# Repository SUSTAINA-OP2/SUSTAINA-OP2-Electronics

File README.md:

<h1 align="center">
    Printed Circuit Boards for SUSTAINA-OP2&trade;
</h1>
<table align="center">
    <tr>
        <td align="center"><a href="./SUSTAINA-Constant-Voltage-Board">Constant Voltage Board</a></td>
        <td align="center"><a href="./SUTAINA-Control-Switches-Board">Control Switches Board</a></td>
        <td align="center"><a href="./SUSTAINA-PMX-Control-Board">PMX Control Board</a></td>
    </tr>
    <tr>
        <td align="center"></td>
        <td align="center"></td>
        <td align="center"></td>
    </tr>
    <tr>
        <td align="center"><a href="./SUSTAINA-Power-Logging-Board">Power Logging Board</a></td>
        <td align="center"><a href="./SUSTAINA-Power-Distribution-Board">Power Distribution Board</a></td>
        <td align="center"><a href="./SUSTAINA-Power-Supply-Switching-Board">Power Supply Switching Board</a></td>
    </tr>
    <tr>
        <td align="center"></td>
        <td align="center"></td>
        <td align="center"></td>
    </tr>
    <tr>
        <td align="center"><a href="./SUSTAINA-SBC-Power-Board">SBC Power Board</a></td>
        <td align="center"><a href="./SUSTAINA-SCI-Extension-Board">SCI Extension Board</a></td>
        <td align="center"><a href="./SUSTAINA-StrainGauge-Sensing-Board">Strain Gauge Sensing Board</a></td>
    </tr>
    <tr>
        <td align="center"></td>
        <td align="center"></td>
        <td align="center"></td>
    </tr>
    <tr>
        <td align="center"><a href="./SUSTAINA-Power-Monitor-Module">Power Monitor Module</a></td>
        <td align="center"><a href="./SUSTAINA-USB-to-Quad-RS-485-Conv-Module">USB to Quad RS-485 Conv. Module</a></td>
        <td align="center"></td>
    </tr>
    <tr>
        <td align="center"></td>
        <td align="center"></td>
        <td align="center"></td>
    </tr>
</table>

> [!NOTE]
> This repository provides design and order data for PCBs of SUSTAINA-OP2&trade;.<br>
> Other SUSTAINA-OP2&trade; contents
> - Mechanical: https://github.com/SUSTAINA-OP/SUSTAINA-OP2
> - Firmware: https://github.com/SUSTAINA-OP/SUSTAINA-OP2-Firmware

## Features of SUSTAINA-OP2&trade;'s PCBs

All PCBs for SUSTAINA-OP are compatible with PCBA, which can reduce production barriers (such as selecting and assembling electronic components) before they are assembled into robots.

The PCB fabrication and PCBA used for all SUSTAINA-OP2 are outsourced to JLCPCB!

> [!WARNING]
> Some components to be assembled on the PCB (e.g. not in stock or not handled)  cannot be assembled using PCBA and must be assembled by yourself.

## Repository Contents

The PCBs of SUSTAINA-OP2&trade; can be divided into two main categories.<br>
The first is "module," which packages sensors, conversion circuits, etc. in functional units on a single board and can be easily replaced.<br>
The second is "board", which is a multifunctional PCB with modules and other components.

### Boards
- [Constant Voltage Board](./SUSTAINA-Constant-Voltage-Board)
- [Control Switches Board](./SUTAINA-Control-Switches-Board)
- [PMX Control Board](./SUSTAINA-PMX-Control-Board)
- [Power Logging Board](./SUSTAINA-Power-Logging-Board)
- [Power Distribution Board](./SUSTAINA-Power-Distribution-Board)
- [Power Supply Switching Board](./SUSTAINA-Power-Supply-Switching-Board)
- [SBC Power Board](./SUSTAINA-SBC-Power-Board)
- [SCI Extension Board](./SUSTAINA-SCI-Extension-Board)
- [StrainGauge Sensing Board](./SUSTAINA-StrainGauge-Sensing-Board)

### Modules
- [Power Monitor Module](./SUSTAINA-Power-Monitor-Module)
- [USB to Quad RS-485 Conv. Module](./SUSTAINA-USB-to-Quad-RS-485-Conv-Module)

## Development Environment
The PCBs for SUSTAINA-OP2&trade; were designed in **Autodesk Eagle 9.6.2**.

## License Information
This product is open source. Please review the [LICENSE(EN)](/LICENSE) / [LICENSE(JA)](/LICENSE-JA) for license information.

This product by Masato Kubotera is licensed under a [CC BY-NC-SA 4.0 DEED](http://creativecommons.org/licenses/by-nc-sa/4.0/).

> [!NOTE]
> **Summary:**
> - **Attribution** — You must give appropriate credit , provide a link to the license, and indicate if changes were made.
> - **NonCommercial** — You may not use the material for commercial purposes.
> - **ShareAlike** — If you remix, transform, or build upon the material, you must distribute your contributions under the same license as the original.

> [!TIP]
> - **Examples of appropriate credit** — [SUSTAINA-OP2&trade;](https://github.com/SUSTAINA-OP/SUSTAINA-OP) &copy; Masato Kubotera (2024) CC BY-NC-SA 4.0 DEED
> >
> - **Reference & Citation**  
>   To reference and/or cite the work contained in this repository, please use the following publications:
>   - Kubotera, M. and Hayashibara, Y.: SUSTAINA-OP&trade;: Kid-sized Open Hardware Platform Humanoid Robot with Emphasis on Sustainability. RoboCup 2023: Robot World Cup XXVI, pp.166–178 (2024) [Springer](https://link.springer.com/chapter/10.1007/978-3-031-55015-7_14)
>
>     **The paper is about SUSTAINA-OP&trade;. Publications on SUSTAINA-OP2&trade; will be published soon.**

## Contact
If you have any questions, please contact the designer of this product, Masato Kubodera, by [E-mail](masatokubotera06@yahoo.co.jp).

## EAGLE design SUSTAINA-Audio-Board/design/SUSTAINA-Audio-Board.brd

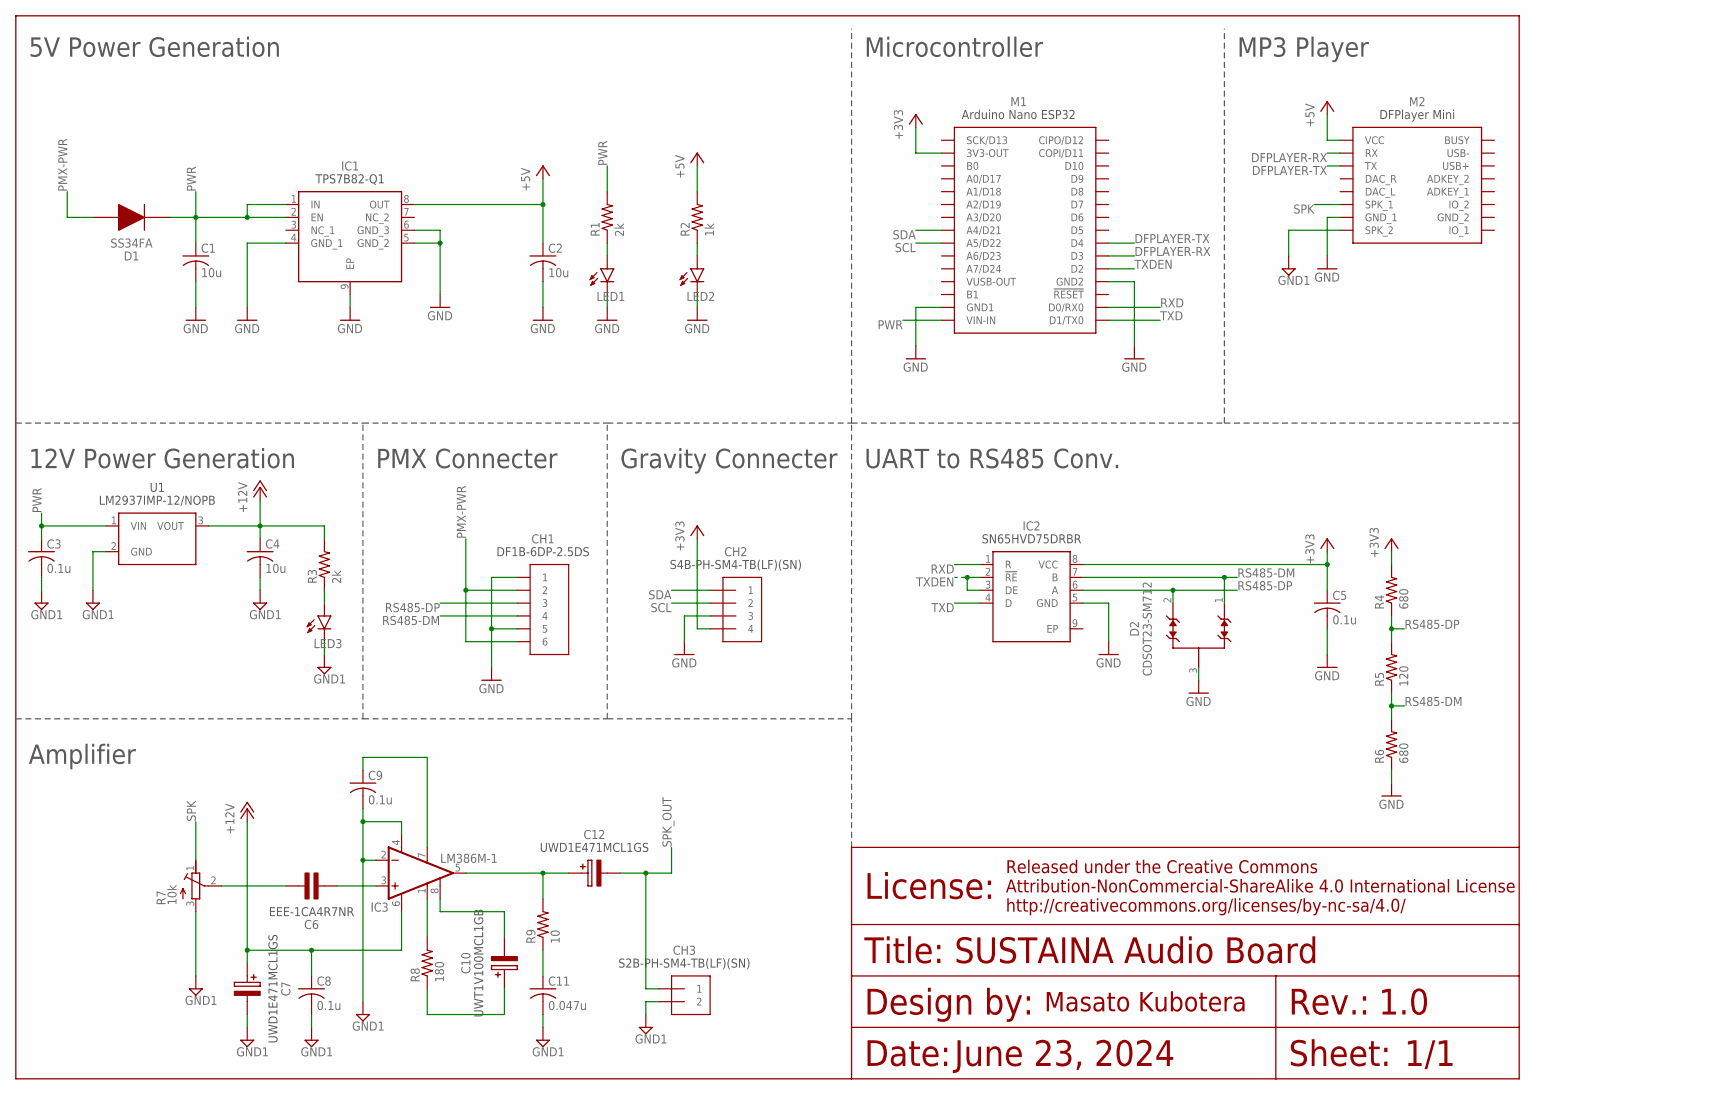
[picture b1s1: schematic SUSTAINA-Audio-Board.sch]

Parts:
C1, C2, C4: 10u; C0603
C3, C5, C8, C9: 0.1u; C0603
C6: EEE-1CA4R7NR
C7, C12: UWD1E471MCL1GS
C10: UWT1V100MCL1GB
C11: 0.047u; C050-055X075
CH1: DF1B-6DP-2.5DS
CH2: S4B-PH-SM4-TB(LF)(SN)
CH3: S2B-PH-SM4-TB(LF)(SN)
D1: SS34FA
D2: CDSOT23-SM712; SOT-23-3
IC1: TPS7B82-Q1; SOP65P490X110-9N
IC2: SN65HVD75DRBR; SON65P300X300X100-9N
IC3: LM386M-1; SO08
LED1, LED2, LED3: LEDSML0603; SML0603
M1: NANO-ESP32
M2: DFPLAYER_MINI
R1, R3: 2k; R0603
R2: 1k; R0603
R4, R6: 680; R0603
R5: 120; R0603
R7: 10k; RTRIM3006P
R8: 180; R0603
R9: 10; R0603
U1: LM2937IMP-12NOPB; SOT-223

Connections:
+3V3: C5.1, CH2.4, IC2.8 (VCC), M1.3V3-OUT, R4.2
+5V: C2.1, IC1.8 (OUT), M2.VCC, R2.2
+12V: C4.1, C7.+, C8.1, IC3.6 (VS), R3.2, U1.3 (VOUT)
DFPLAYER-RX: M1.D3, M2.RX
DFPLAYER-TX: M1.D4, M2.TX
GND: C1.2, C2.2, C5.2, CH1.1, CH1.5, CH2.3, D2.3, IC1.4 (GND_1), IC1.5 (GND_2), IC1.6 (GND_3), IC1.9 (EP), IC2.5 (GND), LED1.C, LED2.C, M1.GND1, M1.GND2, M2.GND_1, R6.1
GND1: C3.2, C4.2, C7.-, C8.2, C9.2, C11.2, CH3.2, IC3.2 (-IN), IC3.4 (GND), LED3.C, M2.SPK2 (SPK_2), R7.3 (A), U1.2 (GND)
LED-5V: LED2.A, R2.1
LED-12V: LED3.A, R3.1
LED-VIN: LED1.A, R1.1
LM386_1: IC3.1 (GAIN), R8.2
LM386_1-8: C10.+, R8.1
LM386_3: C6.1, IC3.3 (+IN)
LM386_3_: C6.2, R7.2 (S)
LM386_7: C9.1, IC3.7 (BYPASS)
LM386_8: C10.-, IC3.8 (GAIN)
PMX-PWR: CH1.2, CH1.6, D1.2
PWR: C1.1, C3.1, D1.1, IC1.1 (IN), IC1.2 (EN), M1.VIN-IN, R1.2, U1.1 (VIN)
RS485-DM: CH1.4, D2.1, IC2.7 (B), R5.1, R6.2
RS485-DP: CH1.3, D2.2, IC2.6 (A), R4.1, R5.2
RXD: IC2.1 (R), M1.D0/RX0
SCL: CH2.2, M1.A5/D22
SDA: CH2.1, M1.A4/D21
SPK: M2.SPK1 (SPK_1), R7.1 (E)
SPK_OUT: C12.-, CH3.1
SPK_OUT_: C12.+, IC3.5 (OUT), R9.2
SPK_OUT__: C11.1, R9.1
TXD: IC2.4 (D), M1.D1/TX0
TXDEN: IC2.2 (!RE), IC2.3 (DE), M1.D2

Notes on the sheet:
1.0
1/1
June 23, 2024
SUSTAINA Audio Board
5V Power Generation
12V Power Generation
PMX Connecter
Gravity Connecter
Amplifier
UART to RS485 Conv.
Microcontroller
MP3 Player

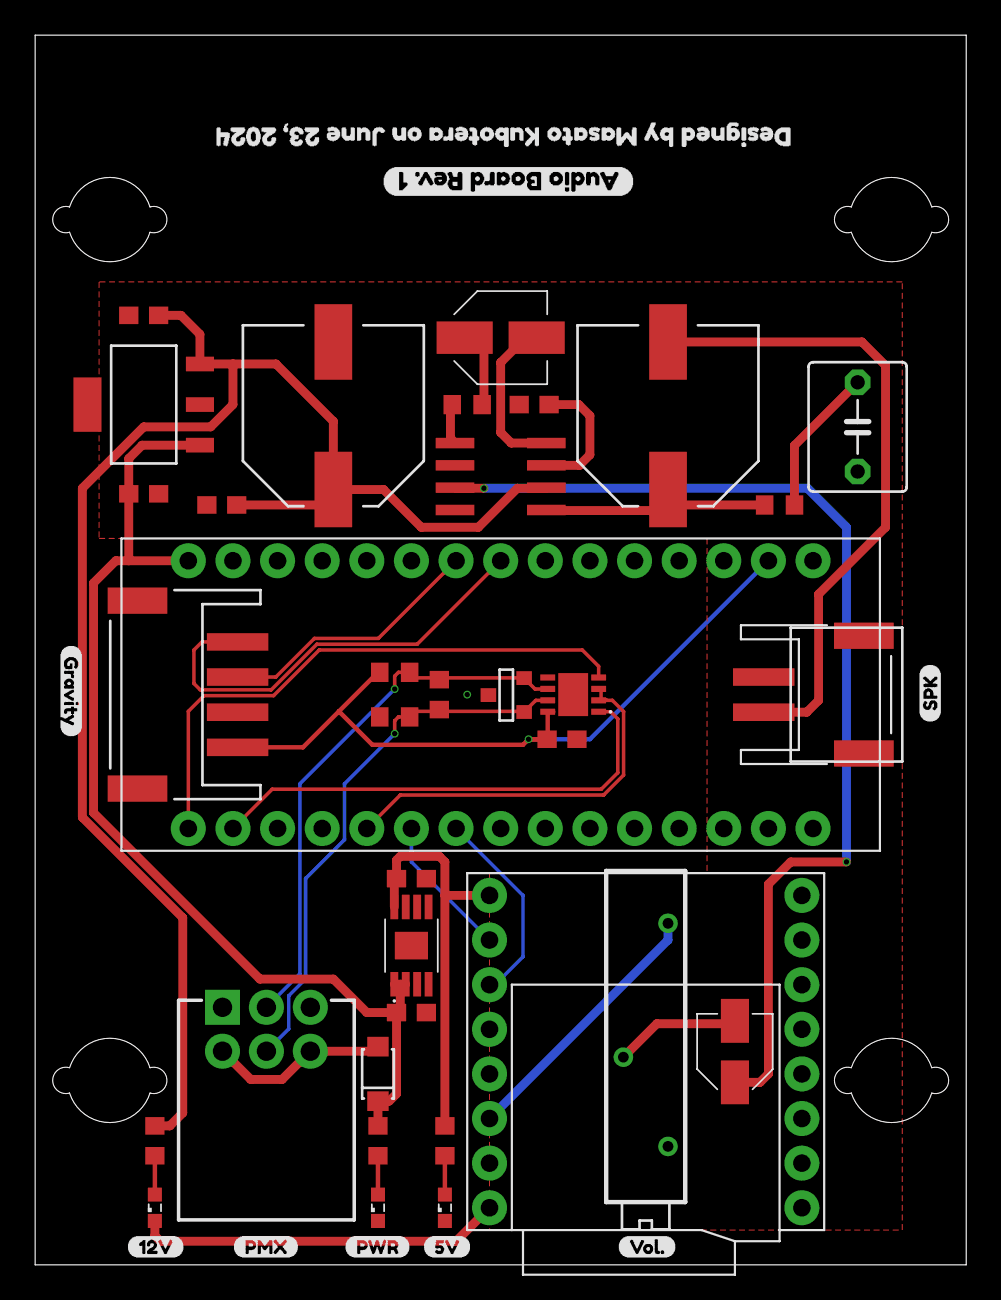
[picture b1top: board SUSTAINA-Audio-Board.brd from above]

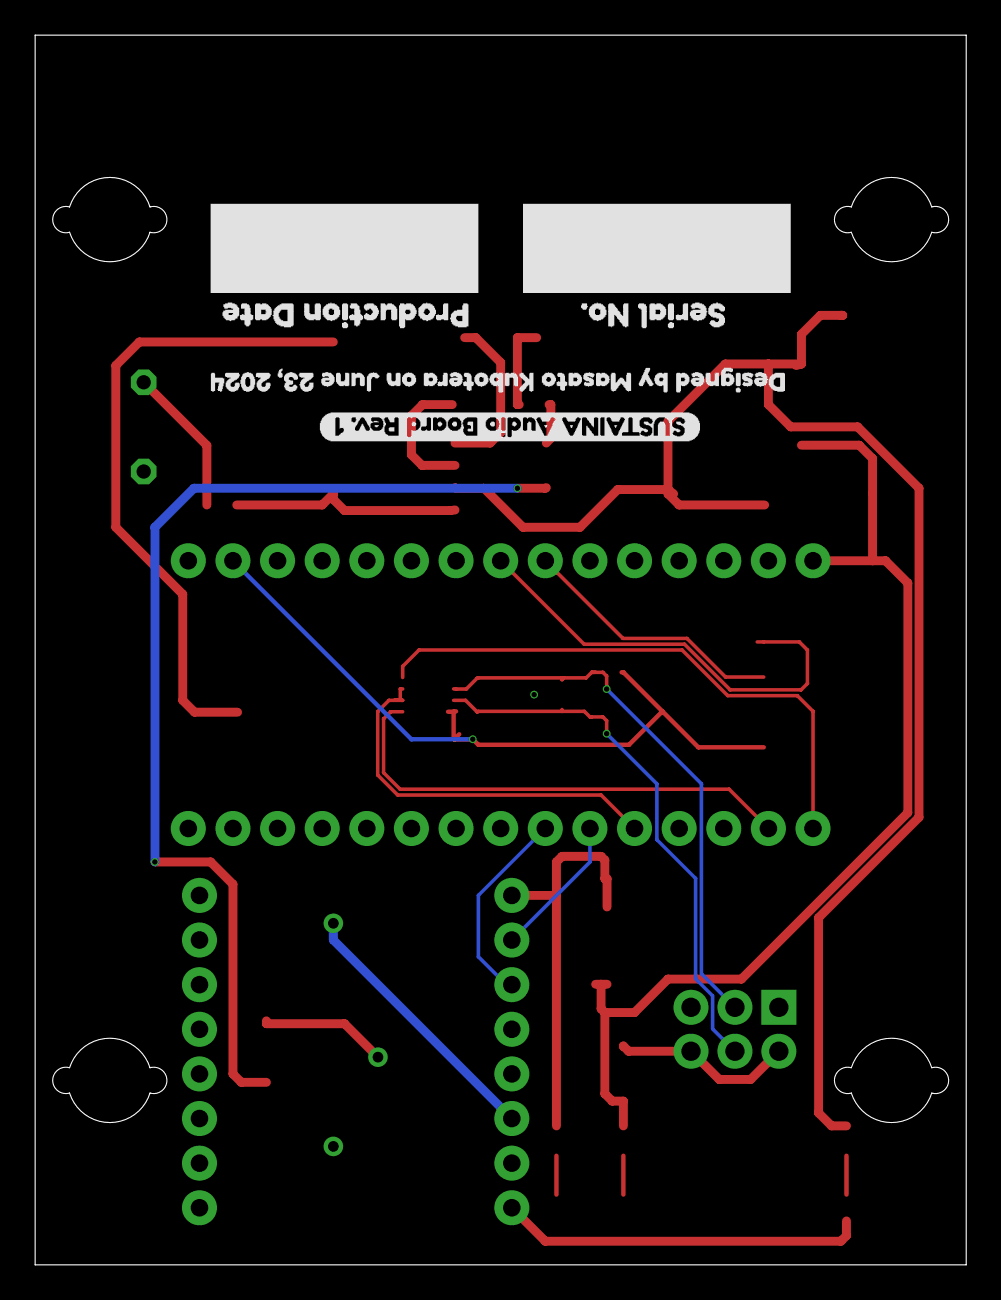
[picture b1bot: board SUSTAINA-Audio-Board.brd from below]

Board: 2 copper layers, 53.0 x 70.0 mm, 48 parts (4 on the bottom side), 29 nets.

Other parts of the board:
U$1: GRAVITY-0.03
U$2, U$11: DESIGNED_BY_MASATO_KUBOTERA_ON_JUNE_23
U$3: 12V-0.03
U$4: 5V-0.03
U$5: PMX-0.03
U$6: PWR-0.03
U$7: VOL#-0.03
U$8: SPK-0.03
U$9: SUSTAINA_AUDIO_BOARD_REV#_1
U$10: AUDIO_BOARD_REV#_1
U$12: PRODUCTION_DATE0
U$13: SERIAL_NO#0

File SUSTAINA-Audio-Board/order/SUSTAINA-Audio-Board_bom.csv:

Comment,Designator,Footprint,LCSC Part #
10u,C1 C2 C4,C0603,C86275
UWT1V100MCL1GB,C10,UWT1V100MCL1GB,C445058
0.1u,C3 C5 C8 C9,C0603,C80516
EEE-1CA4R7NR,C6,EEE-1CA4R7NR,C401604
UWD1E471MCL1GS,C7 C12,UWD1E471MCL1GS,C251022
S4B-PH-SM4-TB(LF)(SN),CH2,S4B-PH-SM4-TB(LF)(SN),C265102
S2B-PH-SM4-TB(LF)(SN),CH3,S2B-PH-SM4-TB(LF)(SN),C295747
SS34FA,D1,SS34FA,C719833
CDSOT23-SM712,D2 ,CDSOT23-SM712,C404012
TPS7B82-Q1,IC1,SOP65P490X110-9N,C424924
SN65HVD75DRBR,IC2,SON65P300X300X100-9N,C98708
LM386M-1,IC3,SO08,C5375298
Green,LED1 LED2 LED3,SML0603,C2922668
2k,R1 R3,R0603,C2097078
1k,R2,R0603,C22548
680,R4 R6,R0603,C112310
120,R5,R0603,C114640
180,R8,R0603,C137786
10,R9,R0603,C109318
LM2937IMP-12NOPB,U1,SOT-223,C5220609

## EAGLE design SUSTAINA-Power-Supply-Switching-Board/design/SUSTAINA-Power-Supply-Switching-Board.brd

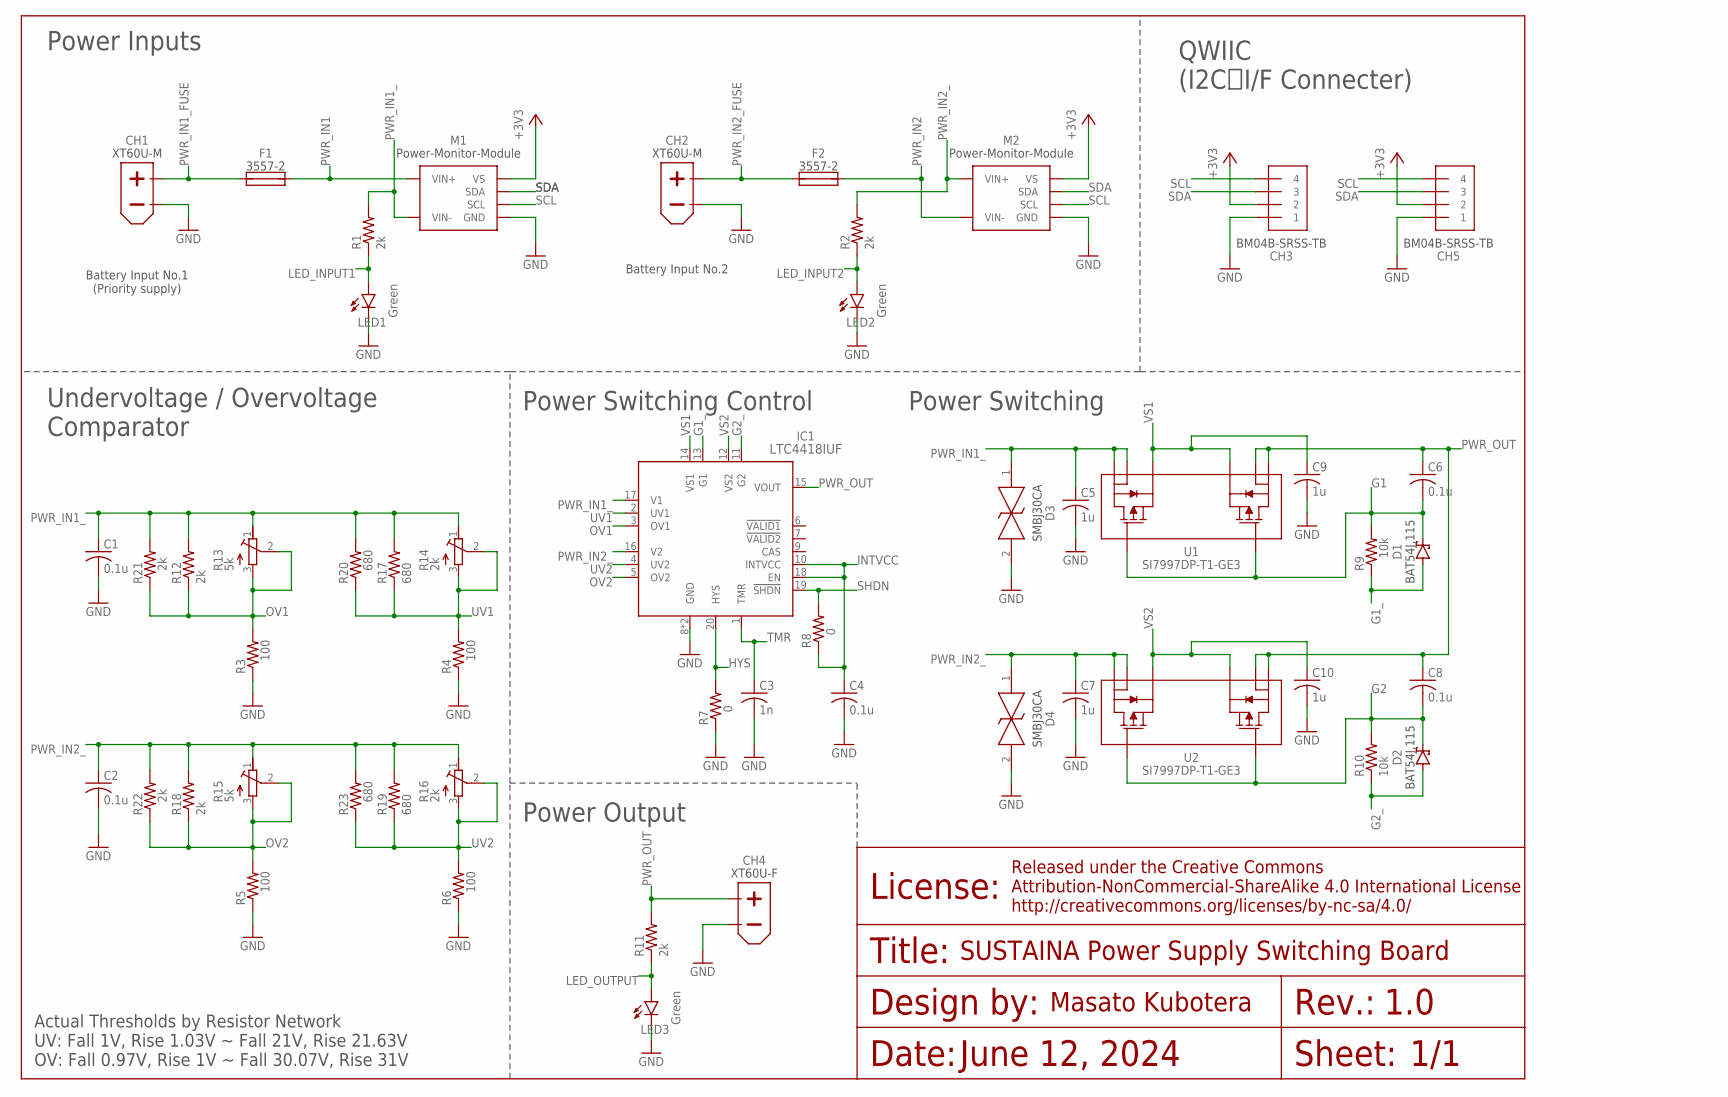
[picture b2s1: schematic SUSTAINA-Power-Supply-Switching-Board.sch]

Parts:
C1, C2, C4, C6, C8: 0.1u; C0603
C3: 1n; C0603
C5, C7, C9, C10: 1u; C0603
CH1, CH2: XT60U-M
CH3, CH5: BM04B-SRSS-TB
CH4: XT60U-F
D1, D2: BAT54J,115; SOD-323-2
D3, D4: SMBJ30CA
F1, F2: 3557-2
IC1: LTC4418IUF
LED1, LED2, LED3: Green; SML0603
M1, M2: POWER-MONITOR-MODULE
R1, R2, R11, R21, R22: 2k; R0603
R3, R4, R5, R6: 100; R0603
R7, R8: 0; R0603
R9, R10: 10k; R0603
R12, R18: 2k; 0204/5
R13, R15: 5k; RTRIM3006P
R14, R16: 2k; RTRIM3006P
R17, R19: 680; 0204/5
R20, R23: 680; R0603
U1, U2: SI7997DP-T1-GE3; POWERPAK_SO-8_VIS

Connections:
+3V3: CH3.2, CH5.2, M1.VS, M2.VS
G1: C6.2, D1.1 (C), R9.2, U1.2 (G1), U1.4 (G2)
G1_: D1.2 (A), IC1.13 (G1), R9.1
G2: C8.2, D2.1 (C), R10.2, U2.2 (G1), U2.4 (G2)
G2_: D2.2 (A), IC1.11 (G2), R10.1
GND: C1.2, C2.2, C3.2, C4.2, C5.2, C7.2, C9.2, C10.2, CH1.-, CH2.-, CH3.1, CH4.-, CH5.1, D3.2, D4.2, IC1.8 (GND), IC1.21 (GND), LED1.C, LED2.C, LED3.C, M1.GND, M2.GND, R3.1, R4.1, R5.1, R6.1, R7.1
HYS: IC1.20 (HYS), R7.2
INTVCC: C4.1, IC1.10 (INTVCC), IC1.18 (EN), R8.1
LED_INPUT1: LED1.A, R1.1
LED_INPUT2: LED2.A, R2.1
LED_OUTPUT: LED3.A, R11.1
OV1: IC1.3 (OV1), R3.2, R12.1, R13.2 (S), R13.3 (A), R21.1
OV2: IC1.5 (OV2), R5.2, R15.2 (S), R15.3 (A), R18.1, R22.1
PWR_IN1: F1.3 (2), F1.4 (2), M1.VIN+1 (VIN+), M1.VIN+2 (VIN+), M1.VIN+3 (VIN+), M1.VIN+4 (VIN+), M1.VIN+5 (VIN+), M1.VIN+6 (VIN+), M1.VIN+7 (VIN+), M1.VIN+8 (VIN+), M1.VIN+9 (VIN+), M1.VIN+10 (VIN+)
PWR_IN1_: C1.1, C5.1, D3.1, IC1.17 (V1), M1.VIN-1 (VIN-), M1.VIN-2 (VIN-), M1.VIN-3 (VIN-), M1.VIN-4 (VIN-), M1.VIN-5 (VIN-), M1.VIN-6 (VIN-), M1.VIN-7 (VIN-), M1.VIN-8 (VIN-), M1.VIN-9 (VIN-), M1.VIN-10 (VIN-), R1.2, R12.2, R13.1 (E), R14.1 (E), R17.2, R20.2, R21.2, U1.5 (D2), U1.6 (D2_2)
PWR_IN1_FUSE: CH1.+, F1.1, F1.2 (1)
PWR_IN2: F2.3 (2), F2.4 (2), M2.VIN-1 (VIN-), M2.VIN-2 (VIN-), M2.VIN-3 (VIN-), M2.VIN-4 (VIN-), M2.VIN-5 (VIN-), M2.VIN-6 (VIN-), M2.VIN-7 (VIN-), M2.VIN-8 (VIN-), M2.VIN-9 (VIN-), M2.VIN-10 (VIN-)
PWR_IN2_: C2.1, C7.1, D4.1, IC1.16 (V2), M2.VIN+1 (VIN+), M2.VIN+2 (VIN+), M2.VIN+3 (VIN+), M2.VIN+4 (VIN+), M2.VIN+5 (VIN+), M2.VIN+6 (VIN+), M2.VIN+7 (VIN+), M2.VIN+8 (VIN+), M2.VIN+9 (VIN+), M2.VIN+10 (VIN+), R2.2, R15.1 (E), R16.1 (E), R18.2, R19.2, R22.2, R23.2, U2.7 (D1), U2.8 (D1_2)
PWR_IN2_FUSE: CH2.+, F2.1, F2.2 (1)
PWR_OUT: C6.1, C8.1, CH4.+, IC1.15 (VOUT), R11.2, U1.7 (D1), U1.8 (D1_2), U2.5 (D2), U2.6 (D2_2)
SCL: CH3.4, CH5.4, M1.SCL, M2.SCL
SDA: CH3.3, CH5.3, M1.SDA, M2.SDA
SHDN: IC1.19 (!SHDN), R8.2
TMR: C3.1, IC1.1 (TMR)
UV1: IC1.2 (UV1), R4.2, R14.2 (S), R14.3 (A), R17.1, R20.1
UV2: IC1.4 (UV2), R6.2, R16.2 (S), R16.3 (A), R19.1, R23.1
VS1: C9.1, IC1.14 (VS1), U1.1 (S1), U1.3 (S2)
VS2: C10.1, IC1.12 (VS2), U2.1 (S1), U2.3 (S2)

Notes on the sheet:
Battery Input No.1 (Priority supply)
Battery Input No.2
Actual Thresholds by Resistor Network UV: Fall 1V, Rise 1.03V ~ Fall 21V, Rise 21.63V OV: Fall 0.97V, Rise 1V ~ Fall 30.07V, Rise 31V
1.0
1/1
June 12, 2024
SUSTAINA Power Supply Switching Board
Power Inputs
Undervoltage / Overvoltage Comparator
Power Switching Control
Power Switching
QWIIC (I2C I/F Connecter)
Power Output

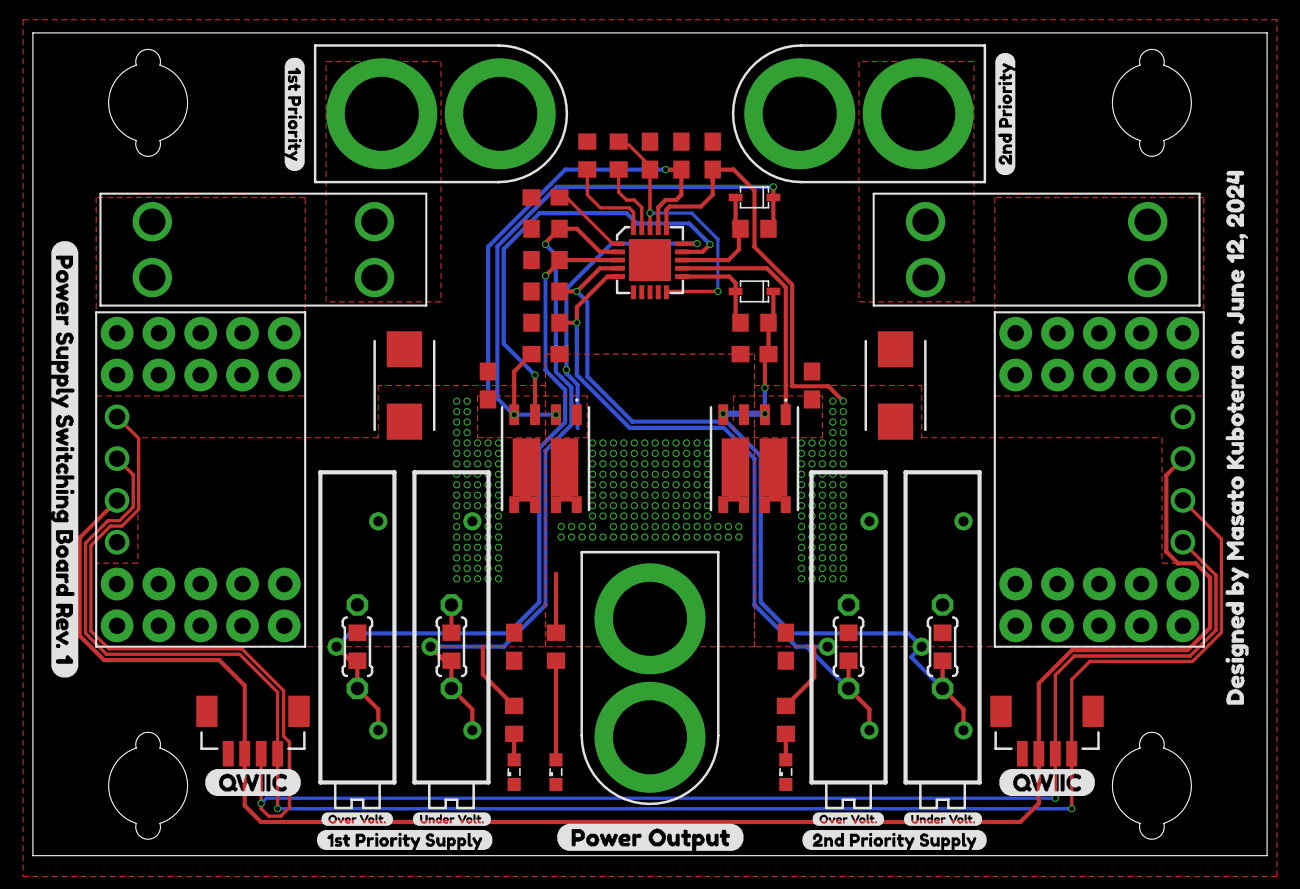
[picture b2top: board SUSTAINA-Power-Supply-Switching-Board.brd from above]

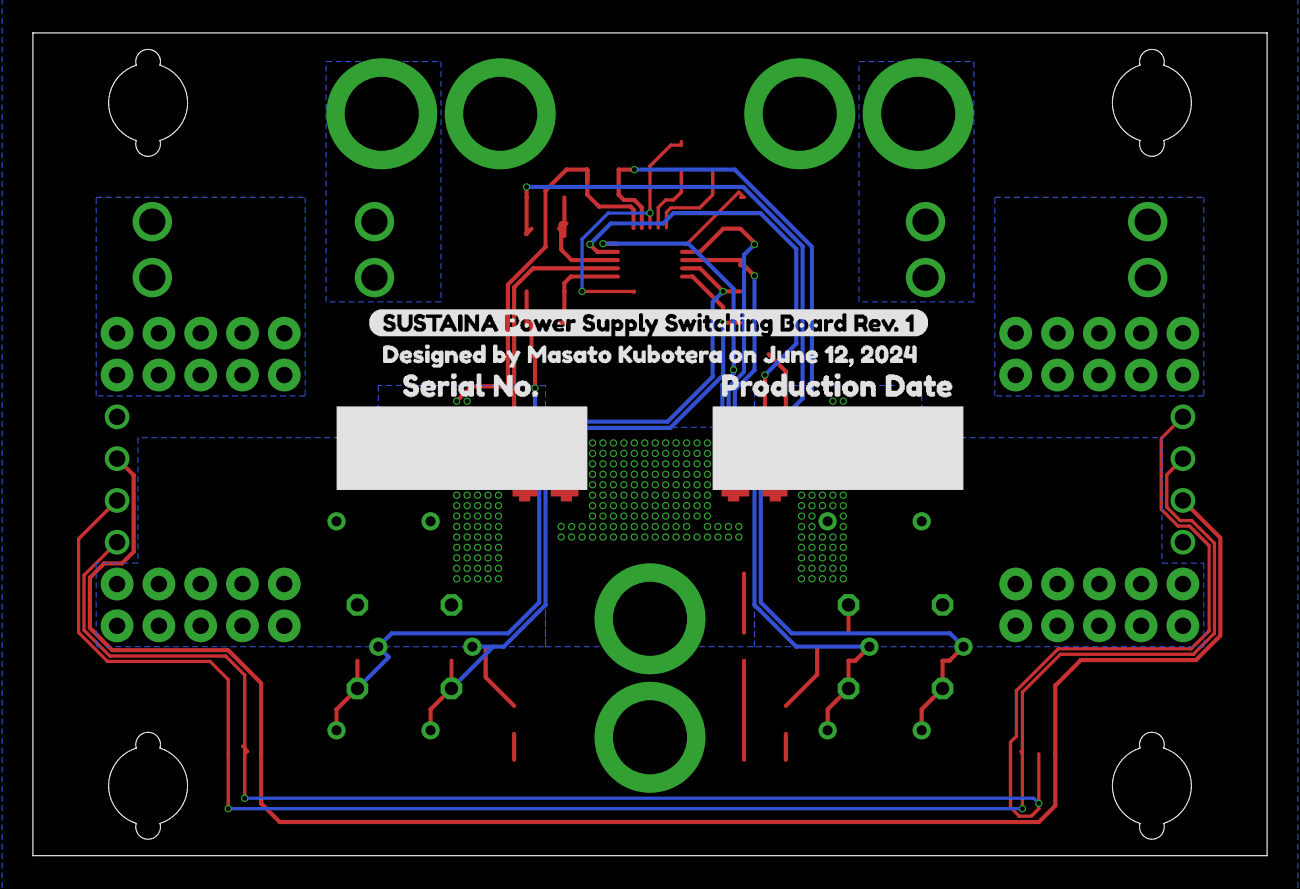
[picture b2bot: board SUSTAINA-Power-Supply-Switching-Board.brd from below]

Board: 2 copper layers, 75.0 x 50.0 mm, 69 parts (4 on the bottom side), 28 nets.

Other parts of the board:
U$1: SUSTAINA_POWER_SUPPLY_SWITCHING_BOARD_REV#_1
U$2, U$15: DESIGNED_BY_MASATO_KUBOTERA_ON_JUNE_12
U$3: 1ST_PRIORITY
U$4: 2ND_PRIORITY
U$5: POWER_OUTPUT0
U$6: 1ST_PRIORITY_SUPPLY1
U$7: 2ND_PRIORITY_SUPPLY1
U$8, U$9: UNDER_VOLT#0
U$10, U$11: OVER_VOLT#0
U$12, U$13: QWIIC0
U$14: POWER_SUPPLY_SWITCHING_BOARD_REV#_1
U$16: SERIAL_NO#0
U$29: PRODUCTION_DATE0

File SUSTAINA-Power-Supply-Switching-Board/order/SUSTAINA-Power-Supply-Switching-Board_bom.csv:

Comment,Designator,Footprint,LCSC Part #
0,R7 R8,R0603,C100044
0.1u,C1 C2 C4 C6 C8,C0603,C2929177
1n,C3,C0603,C153291
1u,C5 C7 C9 C10,C0603,C86020
2k,R1 R2 R11 R21 R22,R0603,C2097078
10k,R9 R10,R0603,C98220
100,R3 R4 R5 R6,R0603,C105588
680,R20 R23,R0603,C112310
BAT54J 115,D1,SOD-323-2,C130415
BAT54J 115,D2,SOD-323-2,C130415
BM04B-SRSS-TB,CH3 CH5,BM04B-SRSS-TB,C160390
Green,LED1 LED2 LED3,SML0603,C2922668
LTC4418IUF,IC1,LTC4418IUF,C580908
SI7997DP-T1-GE3,U1 U2,POWERPAK_SO-8_VIS,C913432
SMBJ30CA,D3 D4,SMBJ30CA,C83847

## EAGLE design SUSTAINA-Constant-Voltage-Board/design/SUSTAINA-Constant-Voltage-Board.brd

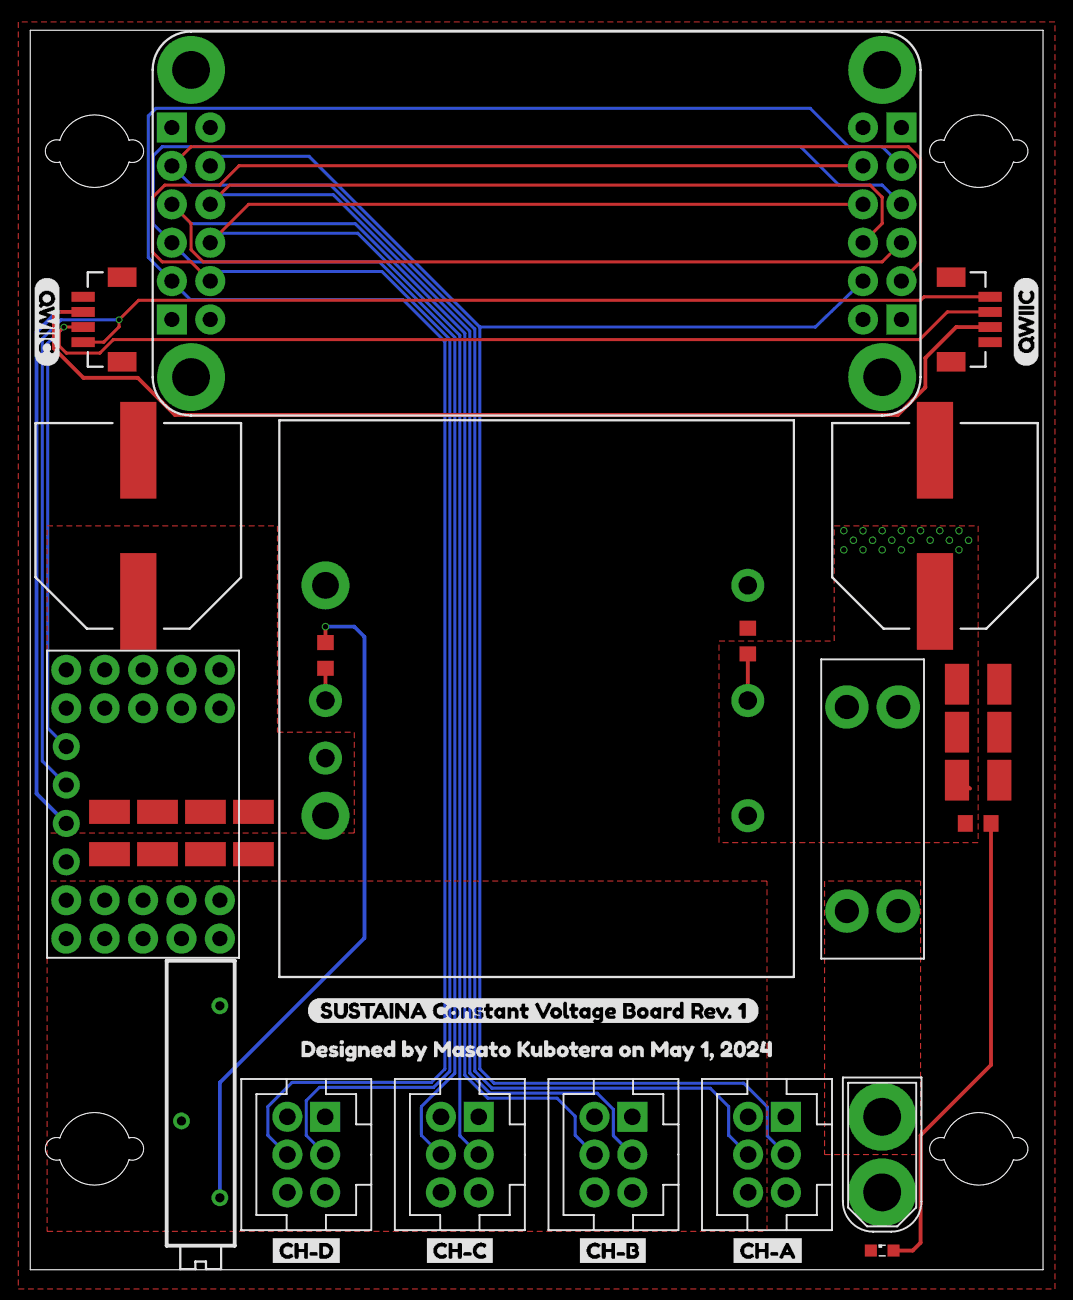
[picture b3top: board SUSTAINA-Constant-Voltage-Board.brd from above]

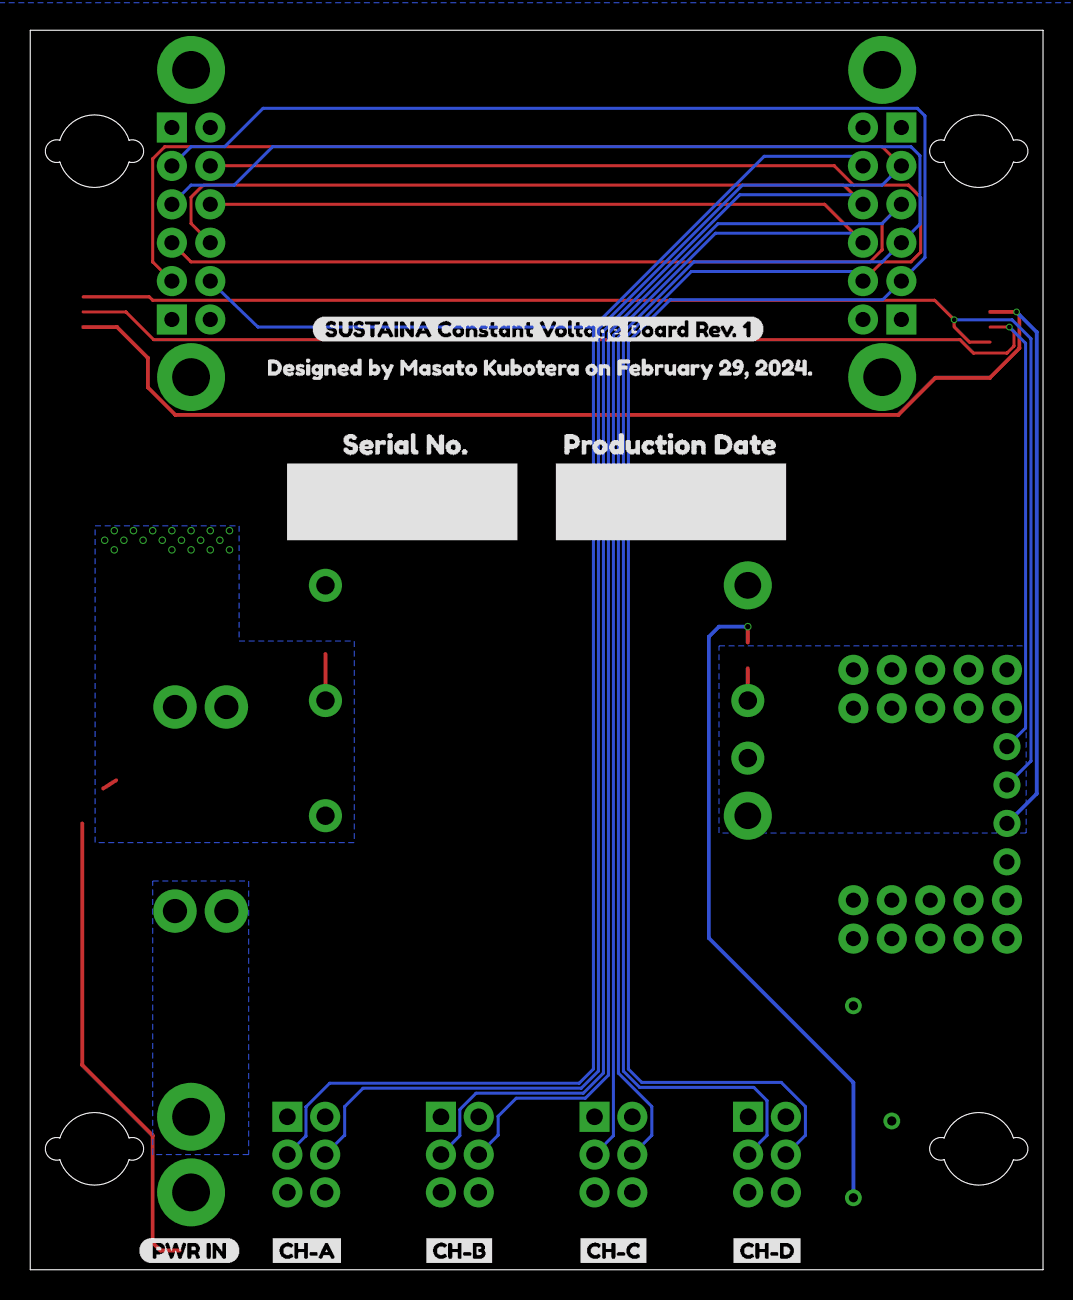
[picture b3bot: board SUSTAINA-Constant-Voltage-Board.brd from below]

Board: 2 copper layers, 67.0 x 82.0 mm, 42 parts (9 on the bottom side), 20 nets.

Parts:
C1, C9: UCM1J361MNJ1MS
C2, C3, C4, C5, C6, C7, C8: 10u; C1210
CH1: XT30U-M
CH2, CH3, CH4, CH5: DF1BZ-6DP-25DSA
CH6, CH7: BM04B-SRSS-TB
F1: 3557-2
LED1: Green; SML0603
M1: I7C4W012A050V-0C1-R; I7C4W012A050V-001-R
M2: POWER-MONITOR-MODULE
M3: USB-TO-QUAD-RS-485-CONV-MODULETPLACE; USB-TO-QUAD-RS-485-CONV-MODULE-TPLACE
R1: 2k; R0603
R2: 0; R0603
R3: 100; R0603
R4: 5k; RTRIM3006P
U$1, U$18: CONSTANT_VOLTAGE_REV#_10; SUSTAINA_CONSTANT_VOLTAGE_BOARD_REV#_1
U$2: DESIGNED_BY_MASATO_KUBOTERA_ON_FEBRUARY_190DESIGN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; DESIGNED_BY_MASATO_KUBOTERA_ON_FEBRUARY_290
U$3: PRODUCTION_DATE0
U$4: SERIAL_NO#0
U$6, U$7: QWIIC0
U$8, U$12: CH#A1
U$9, U$13: CH#B1
U$10, U$14: CH#C1
U$11, U$15: CH#D1
U$16: PWR_IN0
U$17: DESIGNED_BY_MASATO_KUBOTERA_ON_MAY_1

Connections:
+3V3: CH6.2, CH7.2, M2.VS
A-DM: CH2.4, M3.A-RS-485-DM1, M3.A-RS-485-DM2
A-DP: CH2.3, M3.A-RS-485-DP1, M3.A-RS-485-DP2
B-DM: CH3.4, M3.B-RS-485-DM1, M3.B-RS-485-DM2
B-DP: CH3.3, M3.B-RS-485-DP1, M3.B-RS-485-DP2
C-DM: CH4.4, M3.C-RS-485-DM1, M3.C-RS-485-DM2
C-DP: CH4.3, M3.C-RS-485-DP1, M3.C-RS-485-DP2
D-DM: CH5.4, M3.D-RS-485-DM1, M3.D-RS-485-DM2
D-DP: CH5.3, M3.D-RS-485-DP1, M3.D-RS-485-DP2
DCDC_IN: C1.+, C2.1, C3.1, C4.1, F1.3, F1.4, M1.1, R1.2
DCDC_OUT: C5.1, C6.1, C7.1, C8.1, C9.+, M1.7, M1.8, M2.VIN+1, M2.VIN+2, M2.VIN+3, M2.VIN+4, M2.VIN+5, M2.VIN+6, M2.VIN+7, M2.VIN+8, M2.VIN+9, M2.VIN+10
GND: C1.-, C2.2, C3.2, C4.2, C5.2, C6.2, C7.2, C8.2, C9.-, CH1.-, CH2.1, CH2.5, CH3.1, CH3.5, CH4.1, CH4.5, CH5.1, CH5.5, CH6.1, CH7.1, LED1.C, M1.3, M1.4, M2.GND, M3.GND-1, M3.GND-2, M3.GND-3, M3.GND-4, R2.1, R4.1, R4.2
LED_DCDC-IN: LED1.A, R1.1
ONOFF: M1.2, R2.2
PWR_IN: CH1.+, F1.1, F1.2
PWR_OUT: CH2.2, CH2.6, CH3.2, CH3.6, CH4.2, CH4.6, CH5.2, CH5.6, M2.VIN-1, M2.VIN-2, M2.VIN-3, M2.VIN-4, M2.VIN-5, M2.VIN-6, M2.VIN-7, M2.VIN-8, M2.VIN-9, M2.VIN-10
SCL: CH6.4, CH7.4, M2.SCL
SDA: CH6.3, CH7.3, M2.SDA
TRIM: M1.6, R3.2
TRIM_: R3.1, R4.3

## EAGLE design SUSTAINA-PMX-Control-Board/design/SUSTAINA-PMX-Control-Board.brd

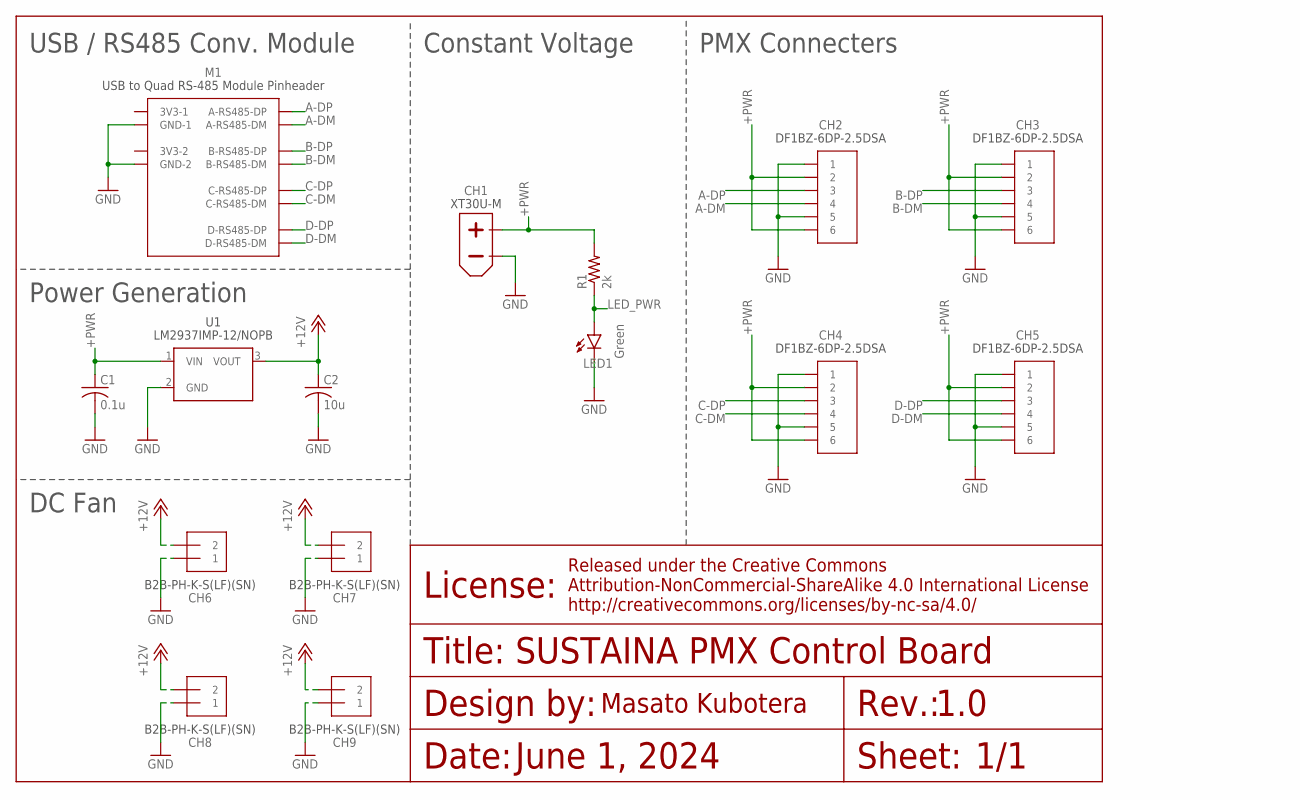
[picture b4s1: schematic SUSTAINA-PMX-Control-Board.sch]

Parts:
C1: 0.1u; C0603
C2: 10u; C0603
CH1: XT30U-M
CH2, CH3, CH4, CH5: DF1BZ-6DP-25DSA
CH6, CH7, CH8, CH9: B2B-PH-K-S(LF)(SN)
LED1: Green; SML0603
M1: USB-TO-QUAD-RS-485-CONV-MODULESINGLE; USB-TO-QUAD-RS-485-CONV-MODULE-TPLACE-SINGLE
R1: 2k; R0603
U1: LM2937IMP-12NOPB; SOT-223

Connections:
+12V: C2.1, CH6.2, CH7.2, CH8.2, CH9.2, U1.3 (VOUT)
+PWR: C1.1, CH1.+, CH2.2, CH2.6, CH3.2, CH3.6, CH4.2, CH4.6, CH5.2, CH5.6, R1.2, U1.1 (VIN)
A-DM: CH2.4, M1.A-RS-485-DM1 (A-RS485-DM)
A-DP: CH2.3, M1.A-RS-485-DP1 (A-RS485-DP)
B-DM: CH3.4, M1.B-RS-485-DM1 (B-RS485-DM)
B-DP: CH3.3, M1.B-RS-485-DP1 (B-RS485-DP)
C-DM: CH4.4, M1.C-RS-485-DM1 (C-RS485-DM)
C-DP: CH4.3, M1.C-RS-485-DP1 (C-RS485-DP)
D-DM: CH5.4, M1.D-RS-485-DM1 (D-RS485-DM)
D-DP: CH5.3, M1.D-RS-485-DP1 (D-RS485-DP)
GND: C1.2, C2.2, CH1.-, CH2.1, CH2.5, CH3.1, CH3.5, CH4.1, CH4.5, CH5.1, CH5.5, CH6.1, CH7.1, CH8.1, CH9.1, LED1.C, M1.GND-1, M1.GND-2, U1.2 (GND)
LED_PWR: LED1.A, R1.1

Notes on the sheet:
June 1, 2024
SUSTAINA PMX Control Board
1.0
1/1
USB / RS485 Conv. Module
PMX Connecters
Constant Voltage
DC Fan
Power Generation

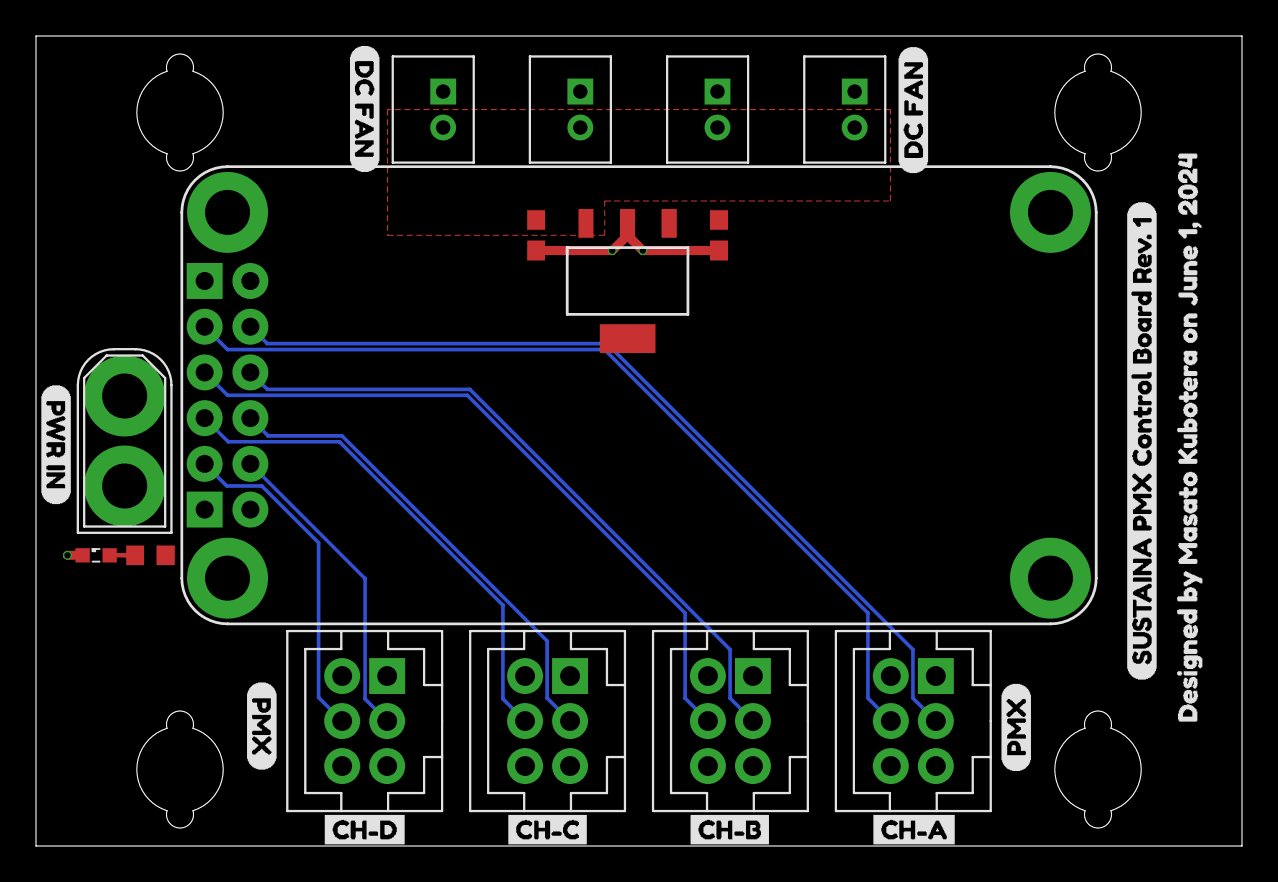
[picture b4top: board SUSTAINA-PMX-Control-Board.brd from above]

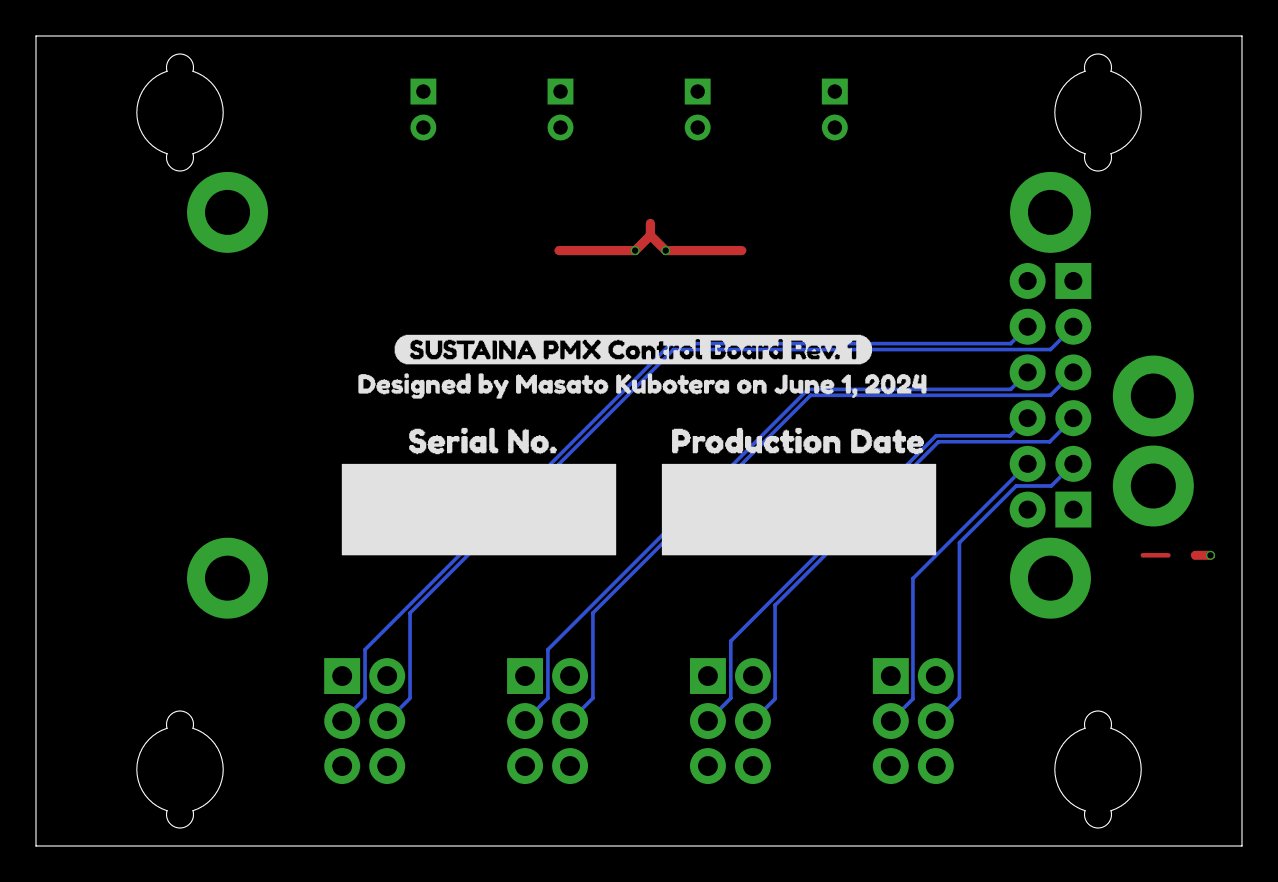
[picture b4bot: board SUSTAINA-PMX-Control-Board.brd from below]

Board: 2 copper layers, 67.0 x 45.0 mm, 30 parts (4 on the bottom side), 12 nets.

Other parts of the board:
U$1, U$2: DESIGNED_BY_MASATO_KUBOTERA_ON_FEBRUARY_190DESIGN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; DESIGNED_BY_MASATO_KUBOTERA_ON_JUNE_1
U$3: PRODUCTION_DATE0
U$4: SERIAL_NO#0
U$5, U$6: PMX
U$7, U$19: DC_FAN
U$8: CH#A1
U$9: CH#B1
U$10: CH#C1
U$11: CH#D1
U$12, U$13: SUSTAINA_PMX_CONTROL_BOARD_REV#_1
U$16: PWR_IN0

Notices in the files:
parts and their libraries:
Frames: Released under the Creative Commons
Attribution-NonCommercial-ShareAlike 4.0 International License
COPYRIGHT: Copyright (C) 2024 Ultra Librarian. All rights reserved.
